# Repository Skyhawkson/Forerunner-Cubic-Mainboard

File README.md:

# Forerunner-Cubic-Mainboard
**NOTE:** Development prior to Rev1.0.1 occurred in a seperate repository

Forerunner Cubic is a small form-factor (55 x 55 x ~70mm) flight controller for high-powered rockets and my personal UAV projects. The mainboard uses an ESP32 WROOM-32D module for a processor, and handles data storage, USB, and Single-Pair Ethernet communication with other future devices. The stacking headers enable a connection to other boards handling:
- RF Communication and Control
- Inertial, air data, and environmental sensors
- Servo and pyrotechnic control
- Battery management and power distribution

Design information is available in the [Schematic](https://github.com/Skyhawkson/Forerunner-Cubic-Mainboard/blob/main/Forerunner%20Cubic%20Mainboard%20Rev1.0.1/Forerunner-Cubic-Mainboard.pdf) as well as the [KiCAD 7 Project File](https://github.com/Skyhawkson/Forerunner-Cubic-Mainboard/tree/main/Forerunner%20Cubic%20Mainboard%20Rev1.0.1/Forerunner-Cubic-Mainboard-Rev1.0.1)

The PCB's outer dimensions measure 50 x 50mm, in order to fit within a standard 3" body tube. 

**Board Images:**

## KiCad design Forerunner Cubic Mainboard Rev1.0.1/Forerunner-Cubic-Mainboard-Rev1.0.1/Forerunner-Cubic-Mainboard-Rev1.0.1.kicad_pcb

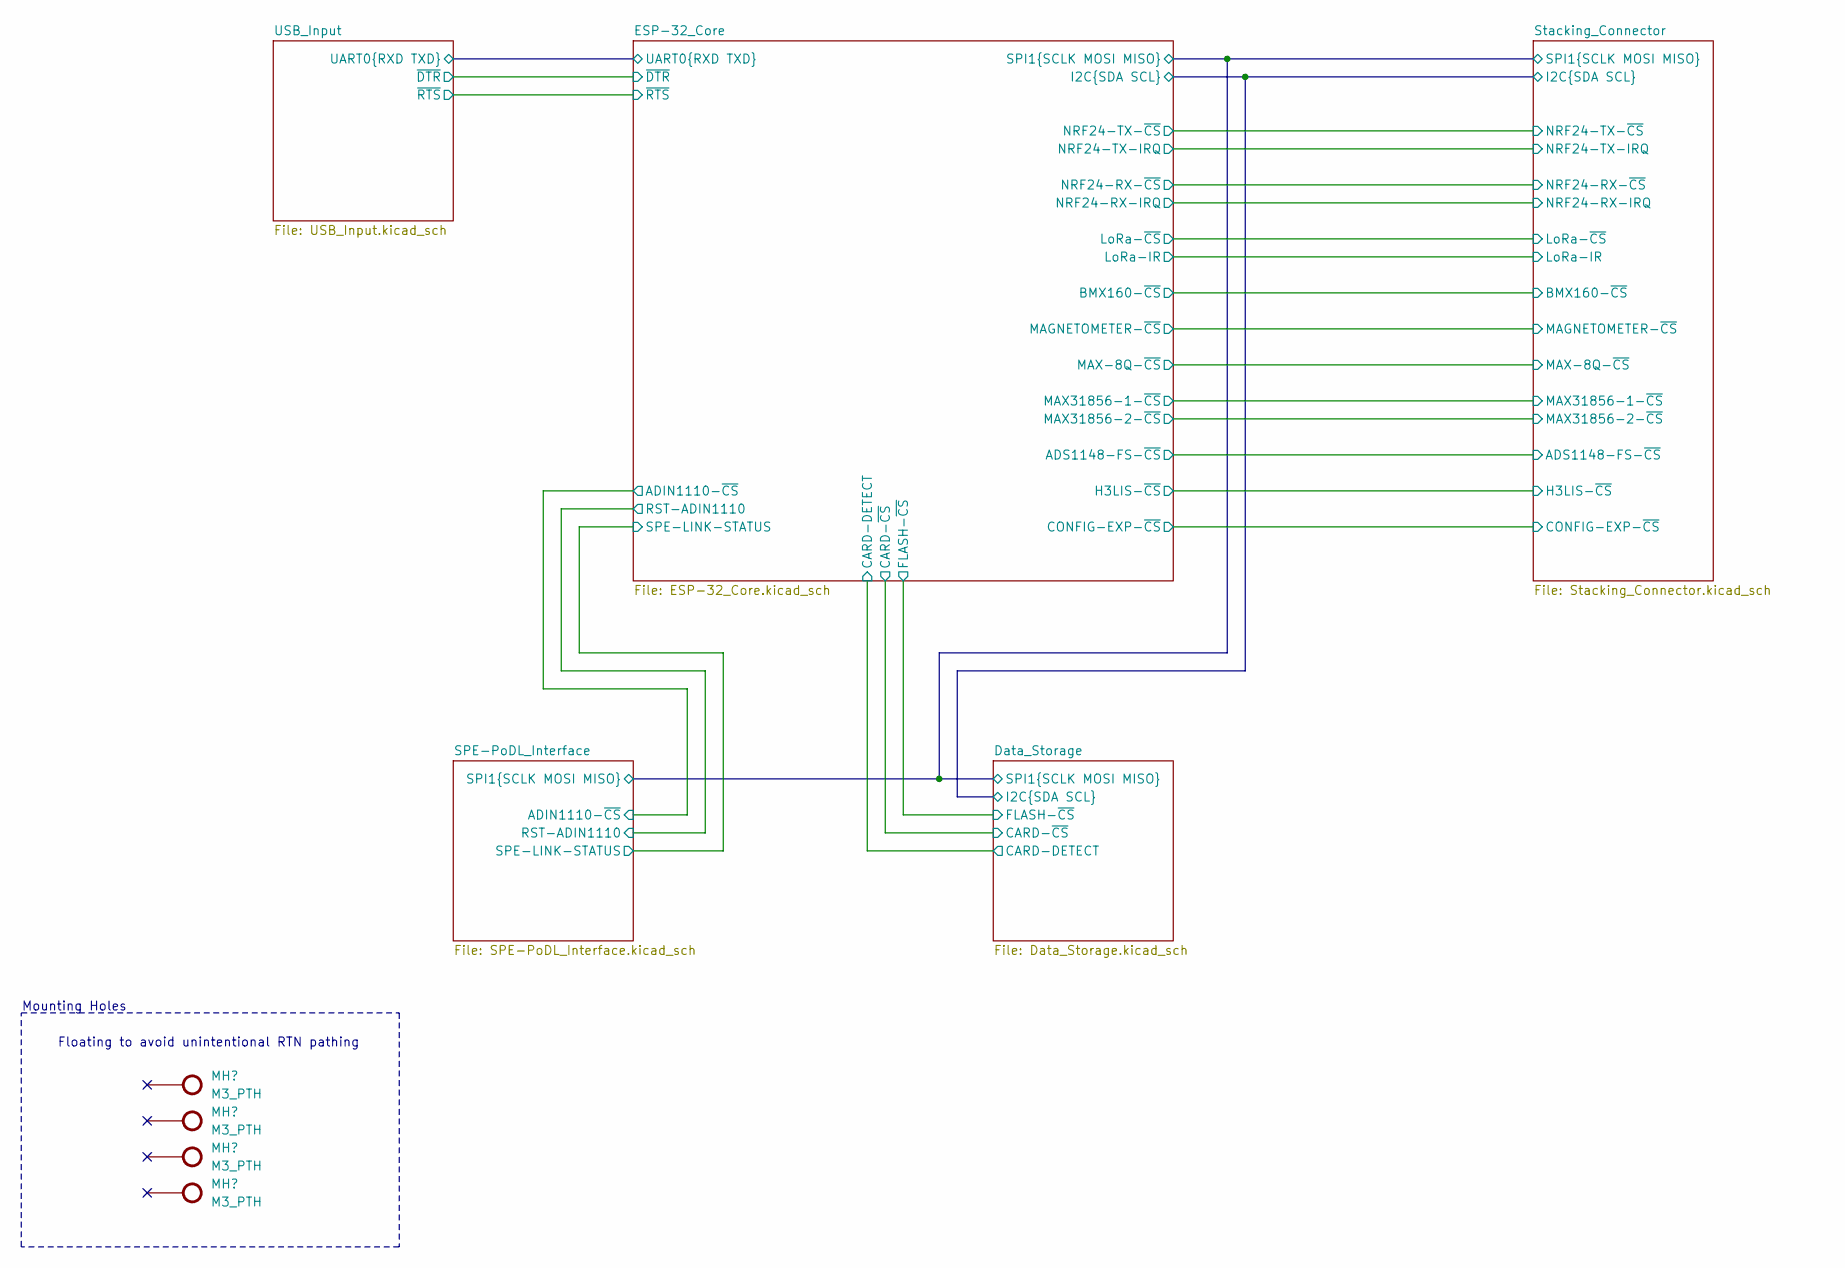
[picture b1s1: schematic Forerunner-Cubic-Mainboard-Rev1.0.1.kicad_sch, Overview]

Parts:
MH1, MH2, MH3, MH4: M3_PTH; GENERIC_MH_M3

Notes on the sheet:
Mounting Holes
Floating to avoid unintentional RTN pathing

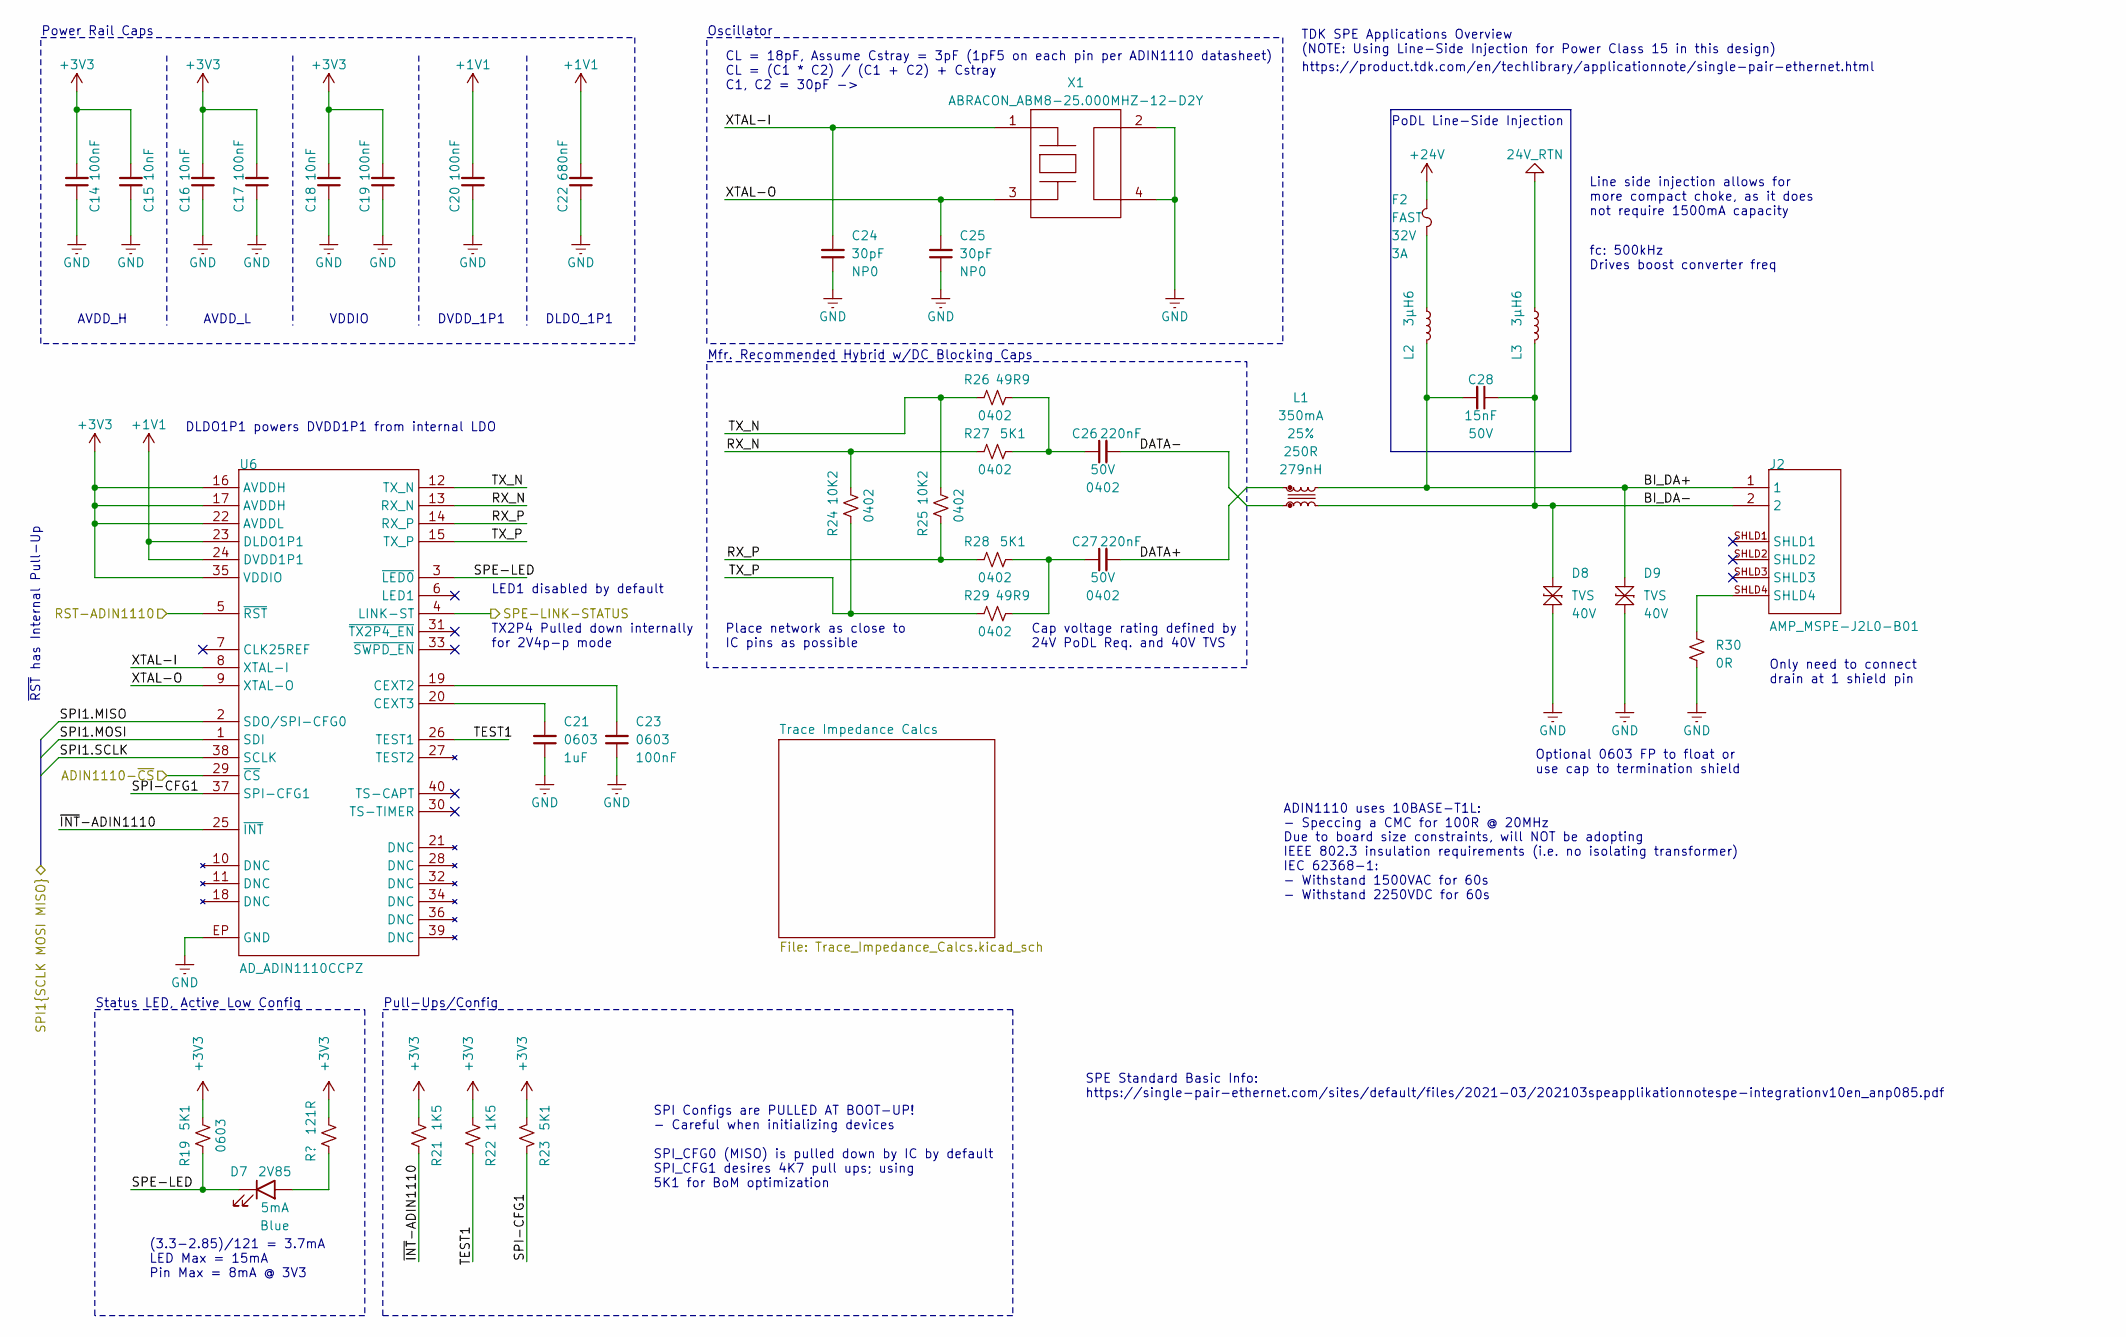
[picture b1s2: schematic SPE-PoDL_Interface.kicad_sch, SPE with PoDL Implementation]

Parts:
C14, C17, C19, C20, C23: 100NF_0603; GENERIC_0603_CAP; Tolerance 10%; Rating 25V
C15, C16, C18: 10NF_0603; GENERIC_0603_CAP; Tolerance 10%; Rating 25V
C21: 1UF_0603; GENERIC_0603_CAP; Tolerance 10%; Rating 25V
C22: 680NF_0603; GENERIC_0603_CAP; Tolerance 20%; Rating 25V
C24, C25: 30PF_0603; GENERIC_0603_CAP; Tolerance 10%; Rating 50V
C26, C27: 220NF_0402; GENERIC_0402_CAP; Tolerance 10%; Rating 50V
C28: 15NF_0603; GENERIC_0603_CAP; Tolerance 10%; Rating 50V
D7: OSRAM_LBQ39E-N1OO-35-1; OSRAM_0603
D8, D9: LF_AXGD10603MR; LF_AXGD1_0603
F2: LF_0494003; LF_0494_(0603); VOLTAGE 32V
J2: AMP_MSPE-J2L0-B01
L1: WE_744230251; WE_CNSW-0603; Tolerance 25%
L2, L3: BOURNS_SRP5030TA-3R6M; BOURNS_SRP5030TA; Tolerance 20%
R19, R23: 5K1_0603; GENERIC_0603_RES; Tolerance 1%
R20: 121R_0603; GENERIC_0603_RES; Tolerance 1%
R21, R22: 1K5_0603; GENERIC_0603_RES; Tolerance 1%
R24, R25: 10K2_0402; GENERIC_0402_RES; Tolerance 1%
R26, R29: 49R9_0402; GENERIC_0402_RES; Tolerance 1%
R27, R28: 5K1_0402; GENERIC_0402_RES; Tolerance 1%
R30: 0R_0603; GENERIC_0603_RES; Tolerance 1%
U6: AD_ADIN1110CCPZ; AD_ADIN1110
X1: ABRACON_ABM8-25.000MHZ-12-D2Y; ABRACON_ABM8

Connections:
24V_RTN: L3.1; also elsewhere on the board
+1V1: C20.2, C22.2, U6.23 (DLDO1P1), U6.24 (DVDD1P1)
+3V3: C14.2, C15.2, C16.2, C17.2, C18.2, C19.2, R19.2, R20.2, R21.2, R22.2, R23.2, U6.16 (AVDDH), U6.17 (AVDDH), U6.22 (AVDDL), U6.35 (VDDIO); also elsewhere on the board
+24V: F2.2; also elsewhere on the board
/Data_Storage/SPI1.MISO: U6.2 (SDO/SPI-CFG0); also elsewhere on the board
/Data_Storage/SPI1.MOSI: U6.1 (SDI); also elsewhere on the board
/Data_Storage/SPI1.SCLK: U6.38 (SCLK); also elsewhere on the board
/ESP-32_Core/ADIN1110-~CS: U6.29 (~CS); also elsewhere on the board
/ESP-32_Core/RST-ADIN1110: U6.5 (~RST); also elsewhere on the board
/ESP-32_Core/SPE-LINK-STATUS: U6.4 (LINK-ST); also elsewhere on the board
/SPE-PoDL_Interface/BI_DA+: C28.2, D9.2, J2.1, L1.2, L2.2
/SPE-PoDL_Interface/BI_DA-: C28.1, D8.2, J2.2, L1.3, L3.2
/SPE-PoDL_Interface/DATA+: C27.2, L1.1
/SPE-PoDL_Interface/DATA-: C26.2, L1.4
/SPE-PoDL_Interface/RX_N: R24.2, R27.1, U6.13 (RX_N)
/SPE-PoDL_Interface/RX_P: R25.1, R28.1, U6.14 (RX_P)
/SPE-PoDL_Interface/SPE-LED: D7.C, R19.1, U6.3 (~LED0)
/SPE-PoDL_Interface/SPI-CFG1: R23.1, U6.37 (SPI-CFG1)
/SPE-PoDL_Interface/TEST1: R22.1, U6.26 (TEST1)
/SPE-PoDL_Interface/TX_N: R25.2, R26.1, U6.12 (TX_N)
/SPE-PoDL_Interface/TX_P: R24.1, R29.1, U6.15 (TX_P)
/SPE-PoDL_Interface/XTAL-I: C24.2, U6.8 (XTAL-I), X1.1
/SPE-PoDL_Interface/XTAL-O: C25.2, U6.9 (XTAL-O), X1.3
/SPE-PoDL_Interface/~INT-ADIN1110: R21.1, U6.25 (~INT)
GND: C14.1, C15.1, C16.1, C17.1, C18.1, C19.1, C20.1, C21.1, C22.1, C23.1, C24.1, C25.1, D8.1, D9.1, R30.1, U6.EP (GND), X1.2, X1.4; also elsewhere on the board
unnamed: C26.1, R26.2, R27.2
unnamed: C27.1, R28.2, R29.2
unnamed: D7.A, R20.1
unnamed: F2.1, L2.1
unnamed: J2.SHLD4, R30.2
unnamed: C23.2, U6.19 (CEXT2)
unnamed: C21.2, U6.20 (CEXT3)

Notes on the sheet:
DLDO1P1 powers DVDD1P1 from internal LDO
Oscillator
DLDO_1P1
LED1 disabled by default
ADIN1110 uses 10BASE-T1L: - Speccing a CMC for 100R @ 20MHz
https://product.tdk.com/en/techlibrary/applicationnote/single-pair-ethernet.html
SPI Configs are PULLED AT BOOT-UP! - Careful when initializing devices SPI_CFG0 (MISO) is pulled down by IC by default SPI_CFG1 desires 4K7 pull ups; using 5K1 for BoM optimization
Place network as close to IC pins as possible
Due to board size constraints, will NOT be adopting IEEE 802.3 insulation requirements (i.e. no isolating transformer) IEC 62368-1: - Withstand 1500VAC for 60s - Withstand 2250VDC for 60s
(3.3-2.85)/121 = 3.7mA LED Max = 15mA Pin Max = 8mA @ 3V3
PoDL Line-Side Injection
Line side injection allows for more compact choke, as it does not require 1500mA capacity
fc: 500kHz Drives boost converter freq
Status LED, Active Low Config
TDK SPE Applications Overview (NOTE: Using Line-Side Injection for Power Class 15 in this design)
TX2P4 Pulled down internally for 2V4p-p mode
Power Rail Caps
SPE Standard Basic Info: https://single-pair-ethernet.com/sites/default/files/2021-03/202103speapplikationnotespe-integrationv10en_anp085.pdf
Cap voltage rating defined by 24V PoDL Req. and 40V TVS
Pull-Ups/Config
VDDIO
AVDD_H
AVDD_L
Optional 0603 FP to float or use cap to termination shield
DVDD_1P1
Mfr. Recommended Hybrid w/DC Blocking Caps
~{RST} has Internal Pull-Up
Only need to connect drain at 1 shield pin
CL = 18pF, Assume Cstray = 3pF (1pF5 on each pin per ADIN1110 datasheet) CL = (C1 * C2) / (C1 + C2) + Cstray C1, C2 = 30pF ->

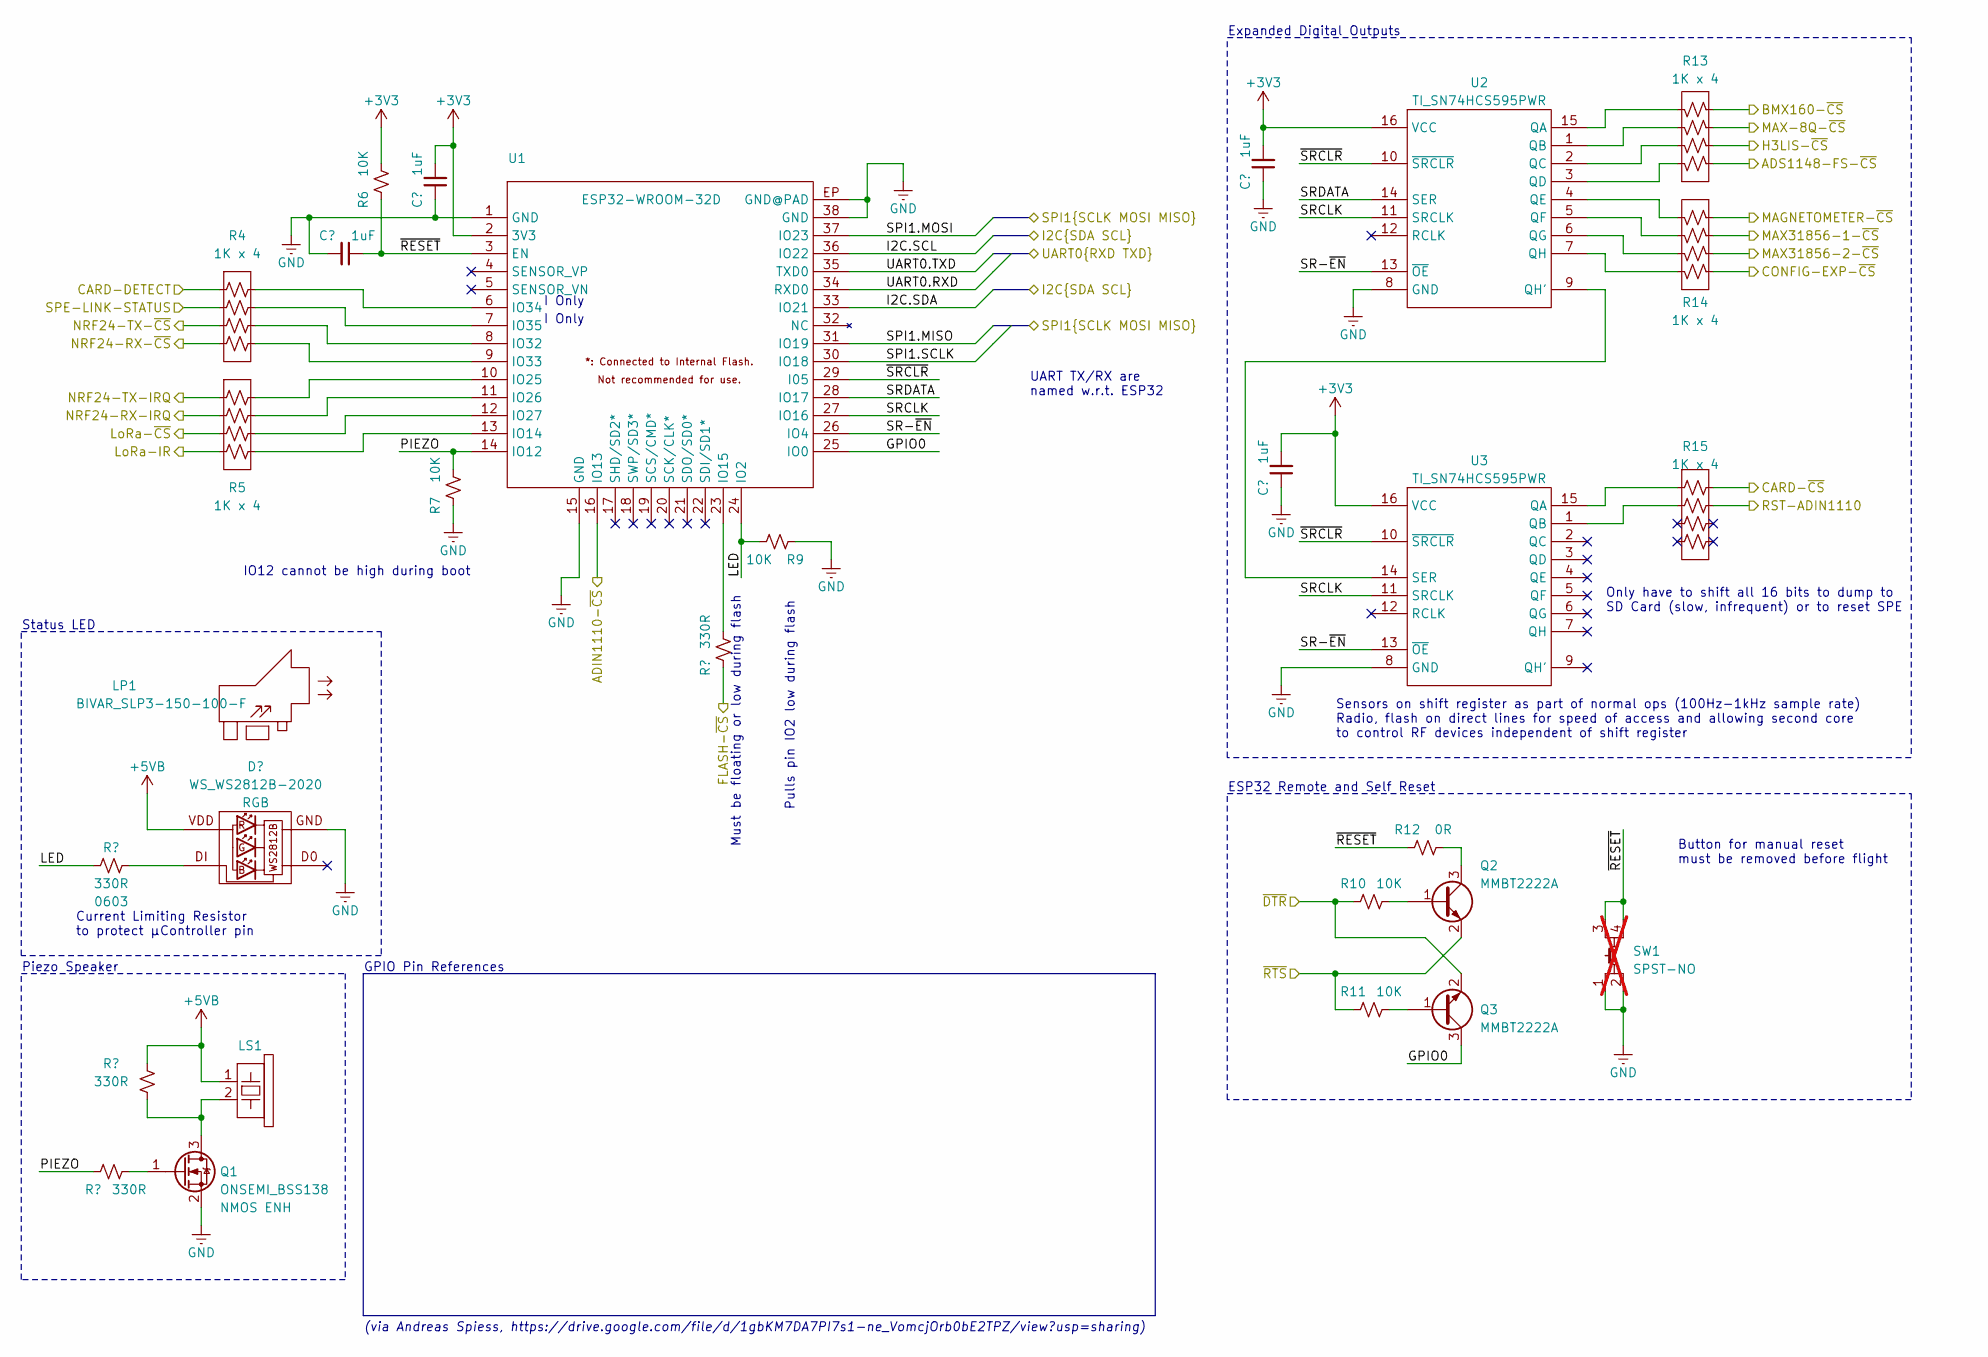
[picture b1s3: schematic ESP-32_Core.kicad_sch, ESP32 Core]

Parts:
C1, C2, C3, C4: 1UF_0805; GENERIC_0805_CAP; Tolerance 10%; Rating 50V
D1: WS_WS2812B-2020
LP1: BIVAR_SLP3-150-100-F
LS1: MURATA_PKMCS0909E4000-R1; MURATA_PKMCS
Q1: ONSEMI_BSS138; GENERIC_SOT-23
Q2, Q3: MMBT2222A; GENERIC_SOT-23
R1, R2, R3, R8: 1K33_0603; GENERIC_0603_RES; Tolerance 1%
R4, R5, R13, R14, R15: CAT16-1001F4LF; BOURNS_CAT16-X4; Tolerance 1%
R6, R7, R9, R10, R11: 10K_0603; GENERIC_0603_RES; Tolerance 1%
R12: 0R_0603; GENERIC_0603_RES; Tolerance 1%
SW1: CK_PTS815-SJG-250-XXXX-LFS; CK_PTS815; not fitted
U1: ESP32-WROOM-32D; ESPRESSIF_ESP-WROOM-32D
U2, U3: TI_SN74HCS595PWR; TI_PW0016A_(TSSOP-16)

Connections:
+3V3: C2.2, C3.2, C4.2, R6.2, U1.2 (3V3), U2.16 (VCC), U3.16 (VCC); also elsewhere on the board
+5VB: D1.4 (VDD), LS1.1, R3.2; also elsewhere on the board
/Data_Storage/CARD-DETECT: R4.1; also elsewhere on the board
/Data_Storage/CARD-~CS: R15.8; also elsewhere on the board
/Data_Storage/FLASH-~CS: R8.1; also elsewhere on the board
/Data_Storage/I2C.SCL: U1.36 (IO22); also elsewhere on the board
/Data_Storage/I2C.SDA: U1.33 (IO21); also elsewhere on the board
/Data_Storage/SPI1.MISO: U1.31 (IO19); also elsewhere on the board
/Data_Storage/SPI1.MOSI: U1.37 (IO23); also elsewhere on the board
/Data_Storage/SPI1.SCLK: U1.30 (IO18); also elsewhere on the board
/ESP-32_Core/ADIN1110-~CS: U1.16 (IO13); also elsewhere on the board
/ESP-32_Core/ADS1148-FS-~CS: R13.8; also elsewhere on the board
/ESP-32_Core/BMX160-~CS: R13.5; also elsewhere on the board
/ESP-32_Core/CONFIG-EXP-~CS: R14.8; also elsewhere on the board
/ESP-32_Core/GPIO0: Q3.3 (C), U1.25 (IO0)
/ESP-32_Core/H3LIS-~CS: R13.7; also elsewhere on the board
/ESP-32_Core/LED: R1.1, R9.2, U1.24 (IO2)
/ESP-32_Core/LoRa-IR: R5.4; also elsewhere on the board
/ESP-32_Core/LoRa-~CS: R5.3; also elsewhere on the board
/ESP-32_Core/MAGNETOMETER-~CS: R14.5; also elsewhere on the board
/ESP-32_Core/MAX31856-1-~CS: R14.6; also elsewhere on the board
/ESP-32_Core/MAX31856-2-~CS: R14.7; also elsewhere on the board
/ESP-32_Core/MAX-8Q-~CS: R13.6; also elsewhere on the board
/ESP-32_Core/NRF24-RX-IRQ: R5.2; also elsewhere on the board
/ESP-32_Core/NRF24-RX-~CS: R4.4; also elsewhere on the board
/ESP-32_Core/NRF24-TX-IRQ: R5.1; also elsewhere on the board
/ESP-32_Core/NRF24-TX-~CS: R4.3; also elsewhere on the board
/ESP-32_Core/PIEZO: R2.1, R7.2, U1.14 (IO12)
/ESP-32_Core/RST-ADIN1110: R15.7; also elsewhere on the board
/ESP-32_Core/SPE-LINK-STATUS: R4.2; also elsewhere on the board
/ESP-32_Core/SR-~EN: U1.26 (IO4), U2.13 (~OE), U3.13 (~OE)
/ESP-32_Core/SRCLK: U1.27 (IO16), U2.11 (SRCLK), U3.11 (SRCLK)
/ESP-32_Core/SRDATA: U1.28 (IO17), U2.14 (SER)
/ESP-32_Core/UART0.RXD: U1.34 (RXD0); also elsewhere on the board
/ESP-32_Core/UART0.TXD: U1.35 (TXD0); also elsewhere on the board
/ESP-32_Core/~DTR: Q3.2 (E), R10.1; also elsewhere on the board
/ESP-32_Core/~RESET: C1.1, R6.1, R12.1, SW1.3, SW1.4, U1.3 (EN)
/ESP-32_Core/~RTS: Q2.2 (E), R11.1; also elsewhere on the board
/ESP-32_Core/~SRCLR: U1.29 (I05), U2.10 (~SRCLR), U3.10 (~SRCLR)
GND: C1.2, C2.1, C3.1, C4.1, D1.2 (GND), Q1.2 (S), R7.1, R9.1, SW1.1, SW1.2, U1.1 (GND), U1.15 (GND), U1.38 (GND), U1.EP (GND@PAD), U2.8 (GND), U3.8 (GND); also elsewhere on the board
unnamed: D1.3 (DI), R1.2
unnamed: LS1.2, Q1.3 (D), R3.1
unnamed: Q1.1 (G), R2.2
unnamed: Q2.1 (B), R10.2
unnamed: Q2.3 (C), R12.2
unnamed: Q3.1 (B), R11.2
unnamed: R5.5, U1.13 (IO14)
unnamed: R8.2, U1.23 (IO15)
unnamed: R5.8, U1.10 (IO25)
unnamed: R5.7, U1.11 (IO26)
unnamed: R5.6, U1.12 (IO27)
unnamed: R4.6, U1.8 (IO32)
unnamed: R4.5, U1.9 (IO33)
unnamed: R4.8, U1.6 (IO34)
unnamed: R4.7, U1.7 (IO35)
unnamed: R13.4, U2.15 (QA)
unnamed: R13.3, U2.1 (QB)
unnamed: R13.2, U2.2 (QC)
unnamed: R13.1, U2.3 (QD)
unnamed: R14.4, U2.4 (QE)
unnamed: R14.3, U2.5 (QF)
unnamed: R14.2, U2.6 (QG)
unnamed: U2.9 (QH'), U3.14 (SER)
unnamed: R14.1, U2.7 (QH)
unnamed: R15.1, U3.15 (QA)
unnamed: R15.2, U3.1 (QB)

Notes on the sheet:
Current Limiting Resistor to protect µController pin
UART TX/RX are named w.r.t. ESP32
Must be floating or low during flash
I Only
Piezo Speaker
Pulls pin IO2 low during flash
GPIO Pin References
Only have to shift all 16 bits to dump to SD Card (slow, infrequent) or to reset SPE
ESP32 Remote and Self Reset
IO12 cannot be high during boot
Button for manual reset must be removed before flight
Expanded Digital Outputs
(via Andreas Spiess, https://drive.google.com/file/d/1gbKM7DA7PI7s1-ne_VomcjOrb0bE2TPZ/view?usp=sharing)
Sensors on shift register as part of normal ops (100Hz-1kHz sample rate) Radio, flash on direct lines for speed of access and allowing second core to control RF devices independent of shift register
Status LED

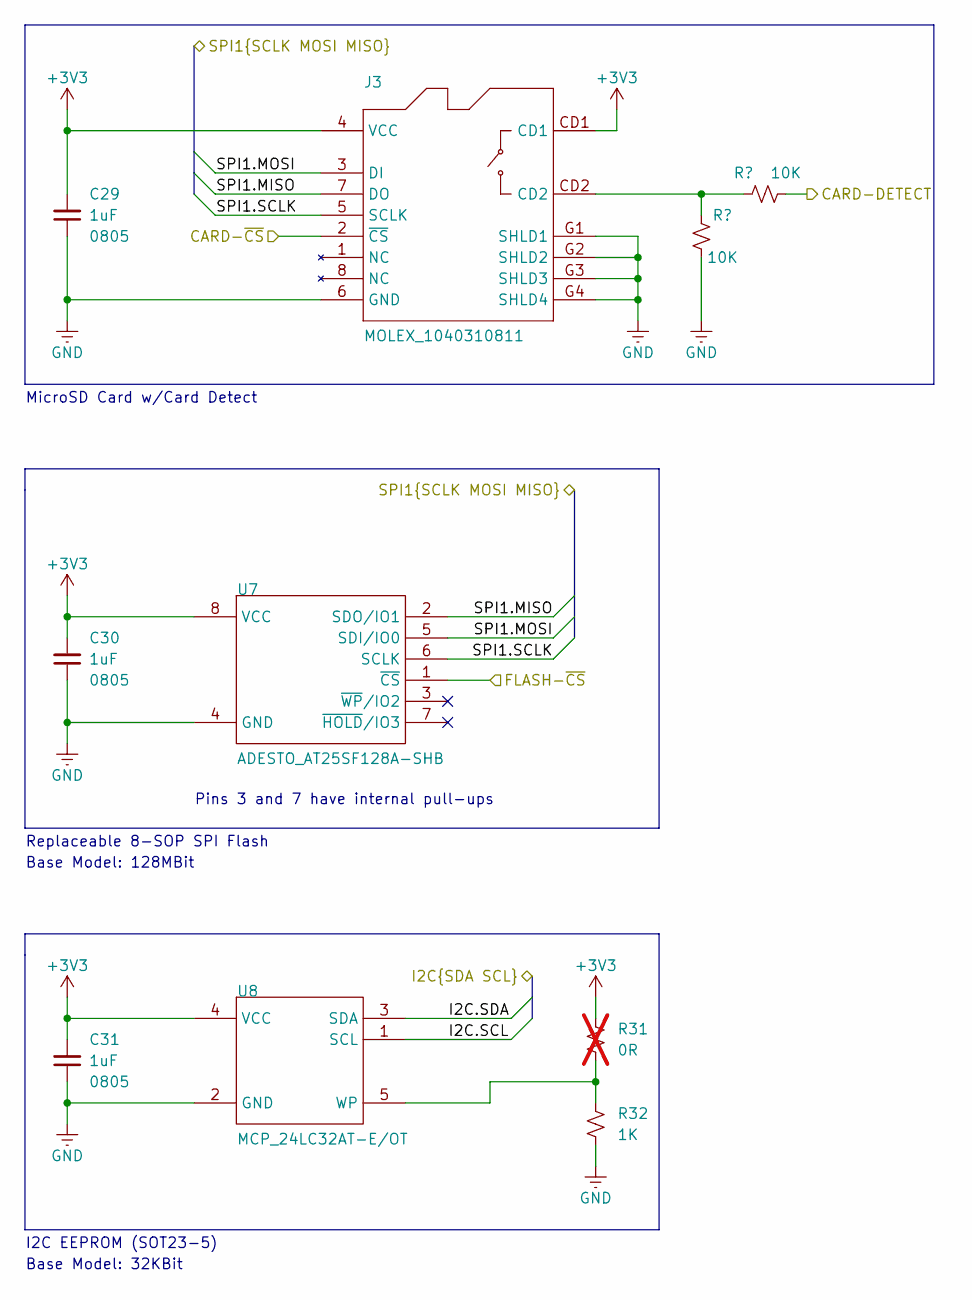
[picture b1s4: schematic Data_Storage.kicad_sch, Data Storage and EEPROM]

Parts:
C29, C30, C31: 1UF_0805; GENERIC_0805_CAP; Tolerance 10%; Rating 50V
J3: MOLEX_1040310811
R31: 0R_0603; GENERIC_0603_RES; Tolerance 1%; not fitted
R32: 1K_0603; GENERIC_0603_RES; Tolerance 1%
R33, R34: 10K_0603; GENERIC_0603_RES; Tolerance 1%
U7: ADESTO_AT25SF128A-SHB; ADESTO_8S4_(SOP-8)
U8: MCP_24LC32AT-E/OT; MCP_SOT23-5

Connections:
+3V3: C29.2, C30.2, C31.2, J3.4 (VCC), J3.CD1, R31.2, U7.8 (VCC), U8.4 (VCC); also elsewhere on the board
/Data_Storage/CARD-DETECT: R34.2; also elsewhere on the board
/Data_Storage/CARD-~CS: J3.2 (~CS); also elsewhere on the board
/Data_Storage/FLASH-~CS: U7.1 (~CS); also elsewhere on the board
/Data_Storage/I2C.SCL: U8.1 (SCL); also elsewhere on the board
/Data_Storage/I2C.SDA: U8.3 (SDA); also elsewhere on the board
/Data_Storage/SPI1.MISO: J3.7 (DO), U7.2 (SDO/IO1); also elsewhere on the board
/Data_Storage/SPI1.MOSI: J3.3 (DI), U7.5 (SDI/IO0); also elsewhere on the board
/Data_Storage/SPI1.SCLK: J3.5 (SCLK), U7.6 (SCLK); also elsewhere on the board
GND: C29.1, C30.1, C31.1, J3.6 (GND), J3.G1 (SHLD1), J3.G2 (SHLD2), J3.G3 (SHLD3), J3.G4 (SHLD4), R32.1, R33.2, U7.4 (GND), U8.2 (GND); also elsewhere on the board
unnamed: J3.CD2, R33.1, R34.1
unnamed: R31.1, R32.2, U8.5 (WP)

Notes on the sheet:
Pins 3 and 7 have internal pull-ups
MicroSD Card w/Card Detect
I2C EEPROM (SOT23-5)
Base Model: 128MBit
Base Model: 32KBit
Replaceable 8-SOP SPI Flash

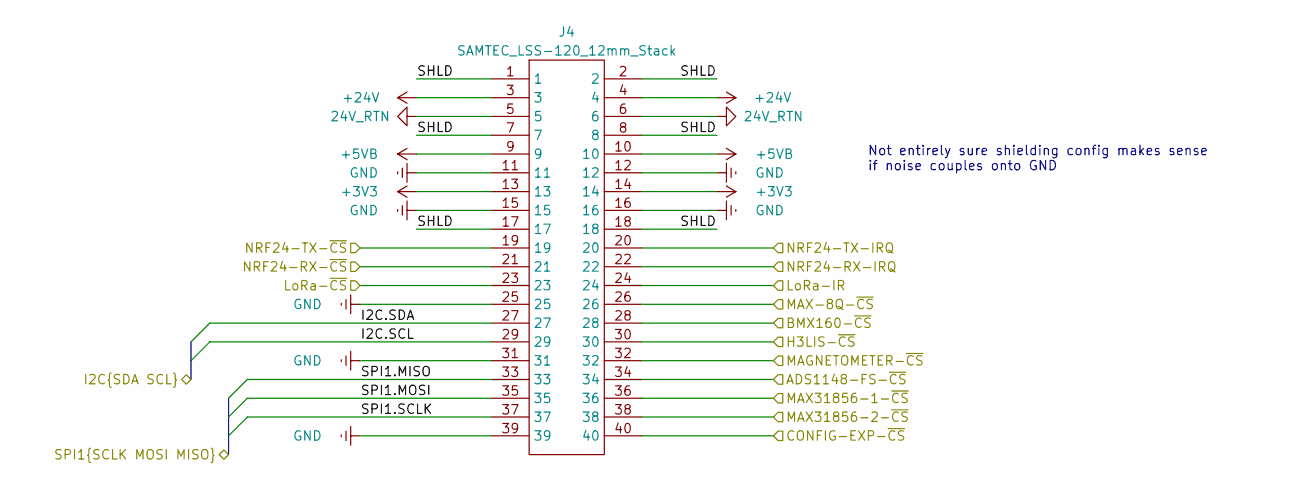
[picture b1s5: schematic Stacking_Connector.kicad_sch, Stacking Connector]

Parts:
J4: SAMTEC_LSS-120_12mm_Stack

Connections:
24V_RTN: J4.5, J4.6; also elsewhere on the board
+3V3: J4.13, J4.14; also elsewhere on the board
+5VB: J4.9, J4.10; also elsewhere on the board
+24V: J4.3, J4.4; also elsewhere on the board
/Data_Storage/I2C.SCL: J4.29; also elsewhere on the board
/Data_Storage/I2C.SDA: J4.27; also elsewhere on the board
/Data_Storage/SPI1.MISO: J4.33; also elsewhere on the board
/Data_Storage/SPI1.MOSI: J4.35; also elsewhere on the board
/Data_Storage/SPI1.SCLK: J4.37; also elsewhere on the board
/ESP-32_Core/ADS1148-FS-~CS: J4.34; also elsewhere on the board
/ESP-32_Core/BMX160-~CS: J4.28; also elsewhere on the board
/ESP-32_Core/CONFIG-EXP-~CS: J4.40; also elsewhere on the board
/ESP-32_Core/H3LIS-~CS: J4.30; also elsewhere on the board
/ESP-32_Core/LoRa-IR: J4.24; also elsewhere on the board
/ESP-32_Core/LoRa-~CS: J4.23; also elsewhere on the board
/ESP-32_Core/MAGNETOMETER-~CS: J4.32; also elsewhere on the board
/ESP-32_Core/MAX31856-1-~CS: J4.36; also elsewhere on the board
/ESP-32_Core/MAX31856-2-~CS: J4.38; also elsewhere on the board
/ESP-32_Core/MAX-8Q-~CS: J4.26; also elsewhere on the board
/ESP-32_Core/NRF24-RX-IRQ: J4.22; also elsewhere on the board
/ESP-32_Core/NRF24-RX-~CS: J4.21; also elsewhere on the board
/ESP-32_Core/NRF24-TX-IRQ: J4.20; also elsewhere on the board
/ESP-32_Core/NRF24-TX-~CS: J4.19; also elsewhere on the board
/Stacking_Connector/SHLD: J4.1, J4.2, J4.7, J4.8, J4.17, J4.18
GND: J4.11, J4.12, J4.15, J4.16, J4.25, J4.31, J4.39; also elsewhere on the board

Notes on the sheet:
Not entirely sure shielding config makes sense if noise couples onto GND

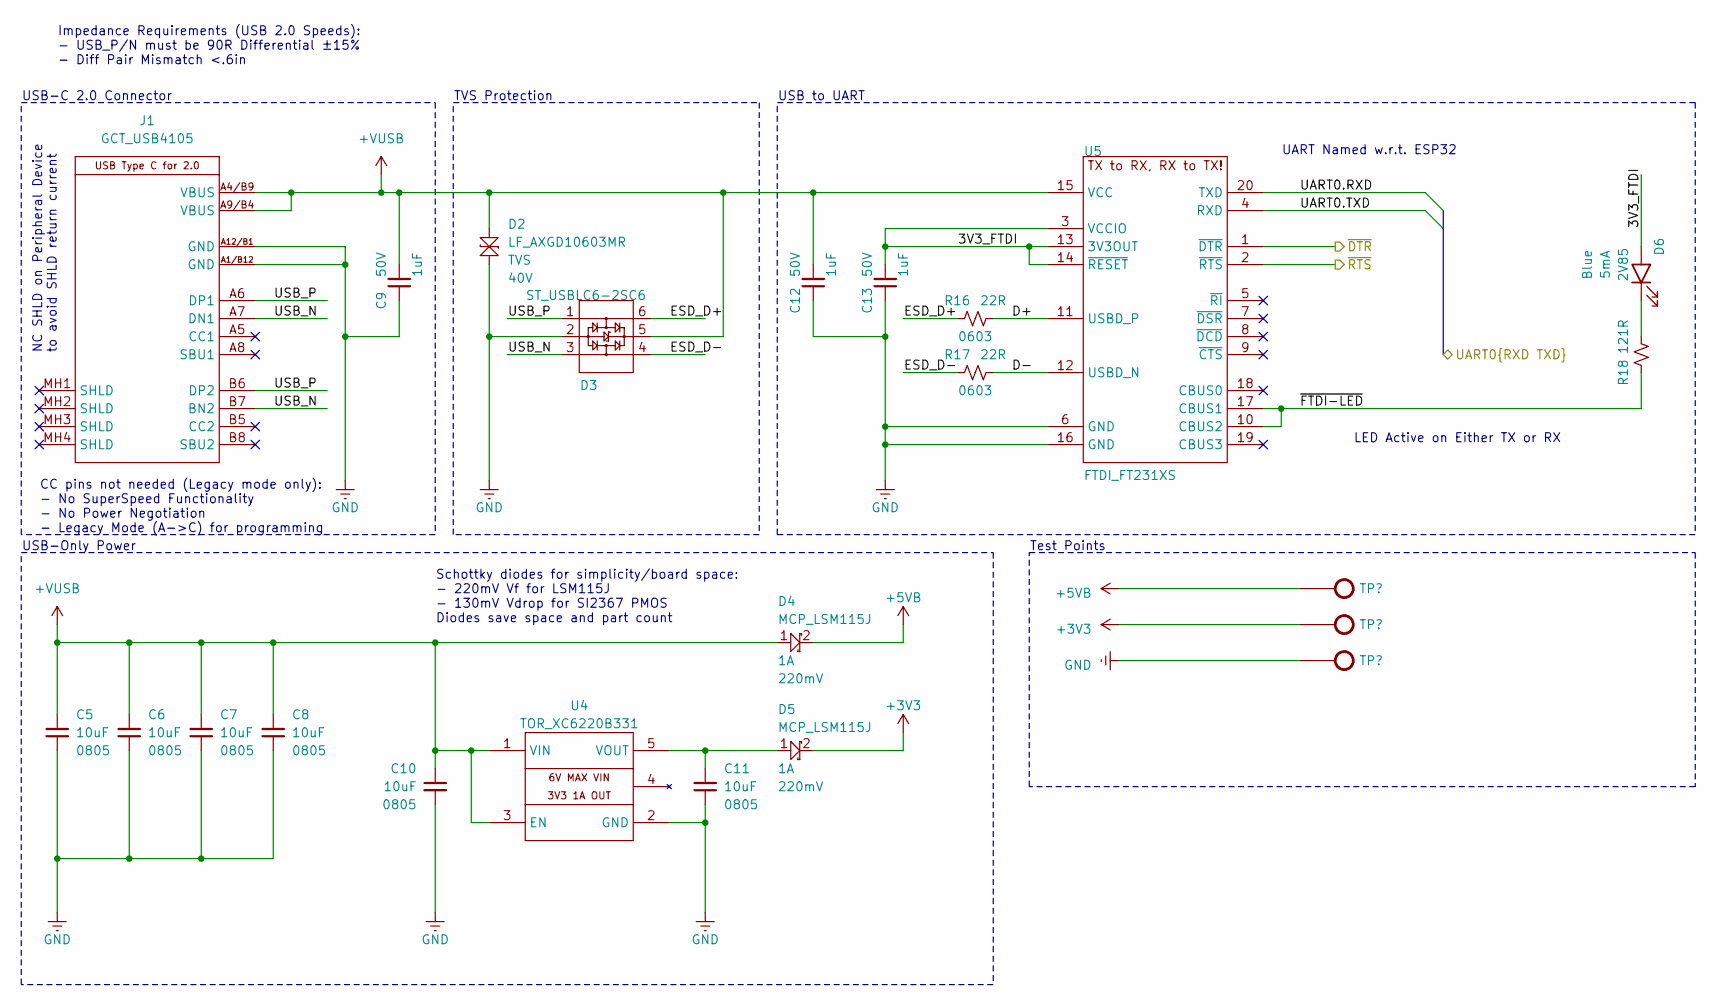
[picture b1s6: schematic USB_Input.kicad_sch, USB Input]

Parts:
C5, C6, C7, C8, C10, C11: 10UF_0805; GENERIC_0805_CAP; Tolerance 10%; Rating 25V
C9, C12, C13: 1UF_0805; GENERIC_0805_CAP; Tolerance 10%; Rating 50V
D2: LF_AXGD10603MR; LF_AXGD1_0603
D3: ST_USBLC6-2SC6; ST_SOT-23-6L
D4, D5: MCP_LSM115J; MCP_DO-214BA
D6: OSRAM_LBQ39E-N1OO-35-1; OSRAM_0603
J1: GCT_USB4105
R16, R17: 22R_0603; GENERIC_0603_RES; Tolerance 1%
R18: 121R_0603; GENERIC_0603_RES; Tolerance 1%
TP1, TP2, TP3: HARWIN_S1751-46; HARWIN_S1751-XX
U4: TOR_XC6220B331; TOR_SOT-25
U5: FTDI_FT231XS; FTDI_000565_(SSOP-20)

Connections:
+3V3: D5.2, TP2.1; also elsewhere on the board
+5VB: D4.2, TP1.1; also elsewhere on the board
+VUSB: C5.2, C6.2, C7.2, C8.2, C9.2, C10.1, C12.2, D2.2, D3.5 (VBUS), D4.1, J1.A4/B9 (VBUS), J1.A9/B4 (VBUS), U4.1 (VIN), U4.3 (EN), U5.15 (VCC)
/ESP-32_Core/UART0.RXD: U5.20 (TXD); also elsewhere on the board
/ESP-32_Core/UART0.TXD: U5.4 (RXD); also elsewhere on the board
/ESP-32_Core/~DTR: U5.1 (~DTR); also elsewhere on the board
/ESP-32_Core/~RTS: U5.2 (~RTS); also elsewhere on the board
/USB_Input/3V3_FTDI: C13.2, D6.A, U5.3 (VCCIO), U5.13 (3V3OUT), U5.14 (~RESET)
/USB_Input/D+: R16.2, U5.11 (USBD_P)
/USB_Input/D-: R17.2, U5.12 (USBD_N)
/USB_Input/ESD_D+: D3.6 (I01), R16.1
/USB_Input/ESD_D-: D3.4 (I02), R17.1
/USB_Input/USB_N: D3.3 (IO2), J1.A7 (DN1), J1.B7 (BN2)
/USB_Input/USB_P: D3.1 (I01), J1.A6 (DP1), J1.B6 (DP2)
/USB_Input/~FTDI-LED: R18.1, U5.10 (CBUS2), U5.17 (CBUS1)
GND: C5.1, C6.1, C7.1, C8.1, C9.1, C10.2, C11.1, C12.1, C13.1, D2.1, D3.2 (GND), J1.A1/B12 (GND), J1.A12/B1 (GND), TP3.1, U4.2 (GND), U5.6 (GND), U5.16 (GND); also elsewhere on the board
unnamed: D6.C, R18.2
unnamed: C11.2, D5.1, U4.5 (VOUT)

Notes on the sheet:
USB to UART
LED Active on Either TX or RX
CC pins not needed (Legacy mode only): - No SuperSpeed Functionality - No Power Negotiation - Legacy Mode (A->C) for programming
USB-Only Power
NC SHLD on Peripheral Device to avoid SHLD return current
UART Named w.r.t. ESP32
TVS Protection
Schottky diodes for simplicity/board space: - 220mV Vf for LSM115J - 130mV Vdrop for SI2367 PMOS Diodes save space and part count
USB-C 2.0 Connector
Test Points
Impedance Requirements (USB 2.0 Speeds): - USB_P/N must be 90R Differential ±15% - Diff Pair Mismatch <.6in

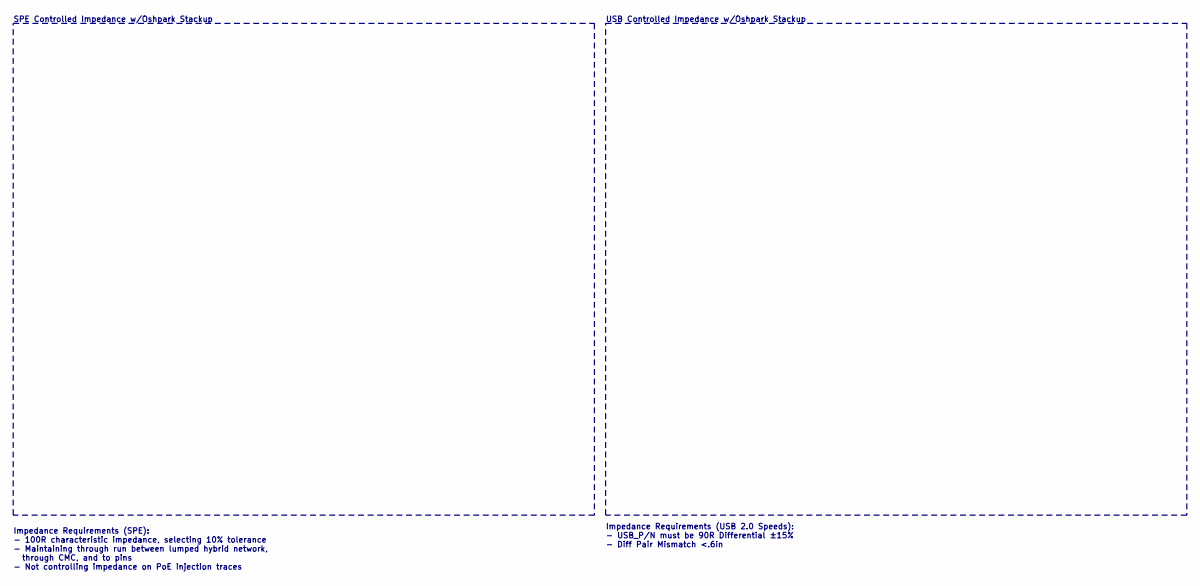
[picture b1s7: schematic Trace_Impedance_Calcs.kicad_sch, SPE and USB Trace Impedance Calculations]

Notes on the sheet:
Impedance Requirements (USB 2.0 Speeds): - USB_P/N must be 90R Differential ±15% - Diff Pair Mismatch <.6in
SPE Controlled Impedance w/Oshpark Stackup
USB Controlled Impedance w/Oshpark Stackup
Impedance Requirements (SPE): - 100R characteristic impedance, selecting 10% tolerance - Maintaining through run between lumped hybrid network, through CMC, and to pins - Not controlling impedance on PoE injection traces

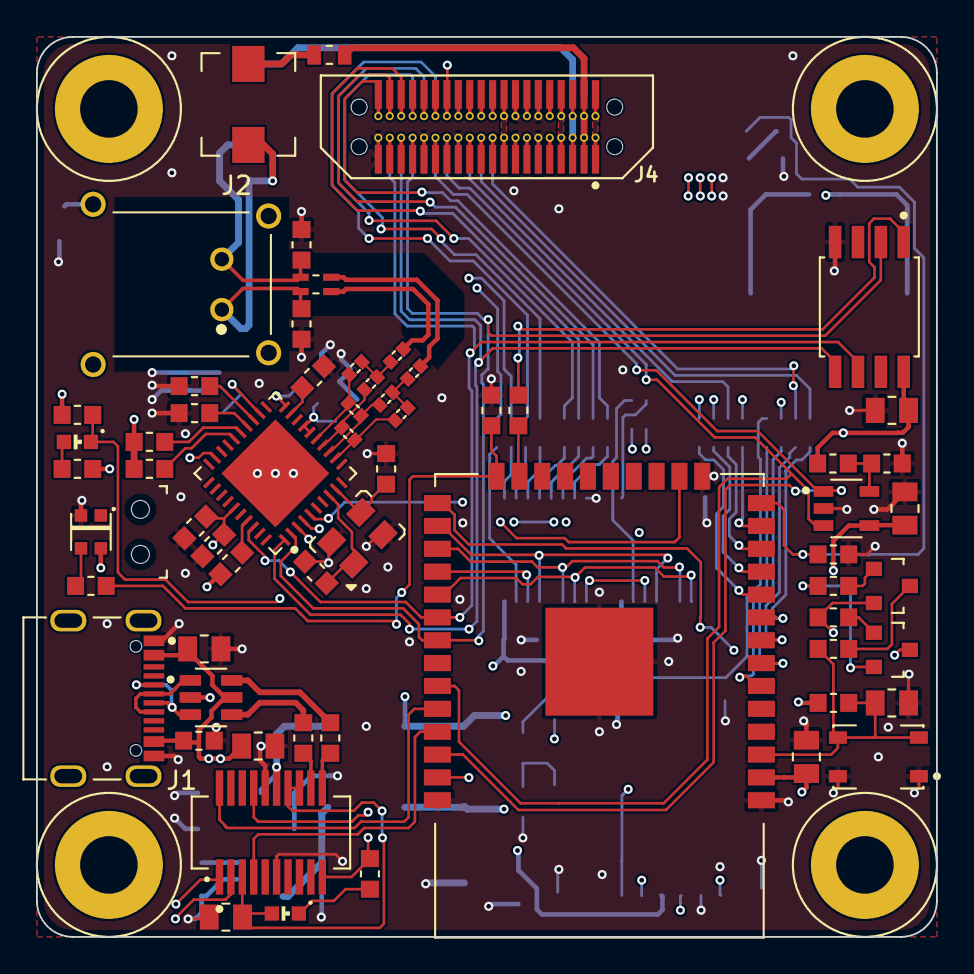
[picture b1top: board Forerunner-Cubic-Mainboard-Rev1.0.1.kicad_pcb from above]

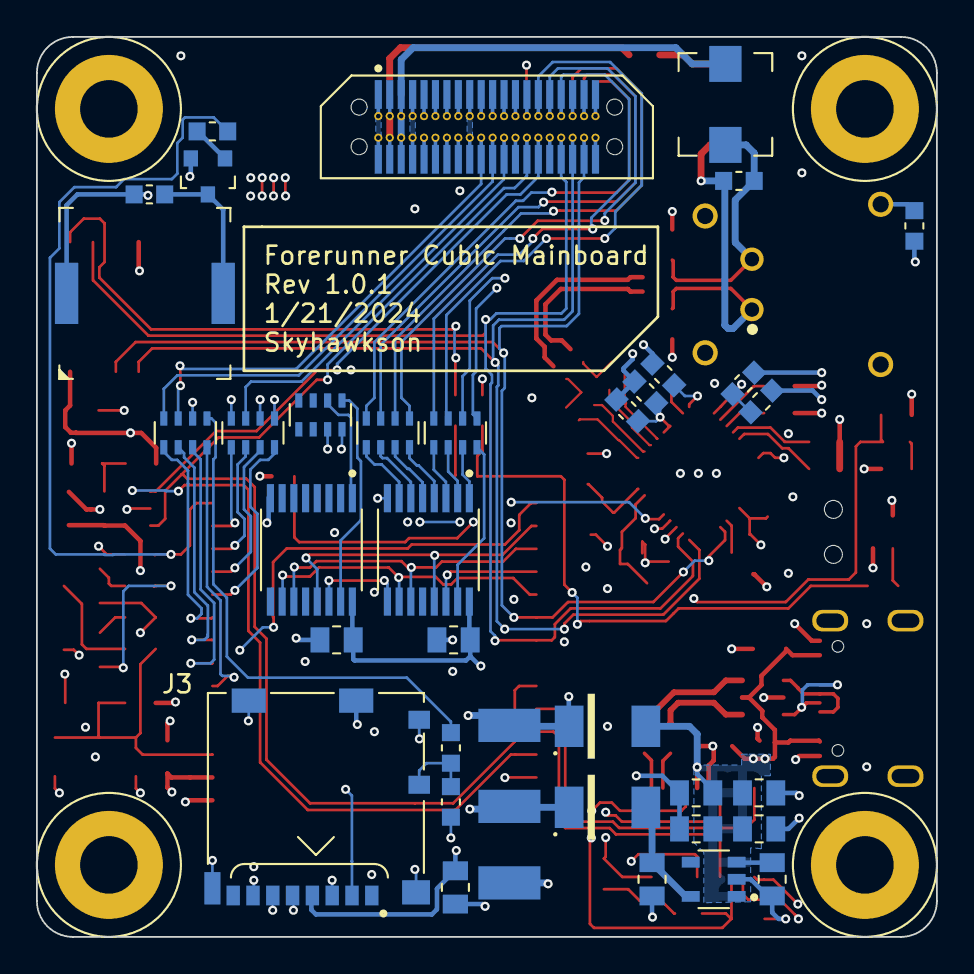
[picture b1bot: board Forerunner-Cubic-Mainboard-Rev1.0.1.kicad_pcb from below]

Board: 4 copper layers, 50.0 x 50.0 mm, 104 parts (37 on the bottom side), 104 nets.

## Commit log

2024-02-05 Add Rev1.0.1 Release Files
    Added files from Rev1.0.1 Release from another repository
2024-02-05 Added System-Level Documentation
